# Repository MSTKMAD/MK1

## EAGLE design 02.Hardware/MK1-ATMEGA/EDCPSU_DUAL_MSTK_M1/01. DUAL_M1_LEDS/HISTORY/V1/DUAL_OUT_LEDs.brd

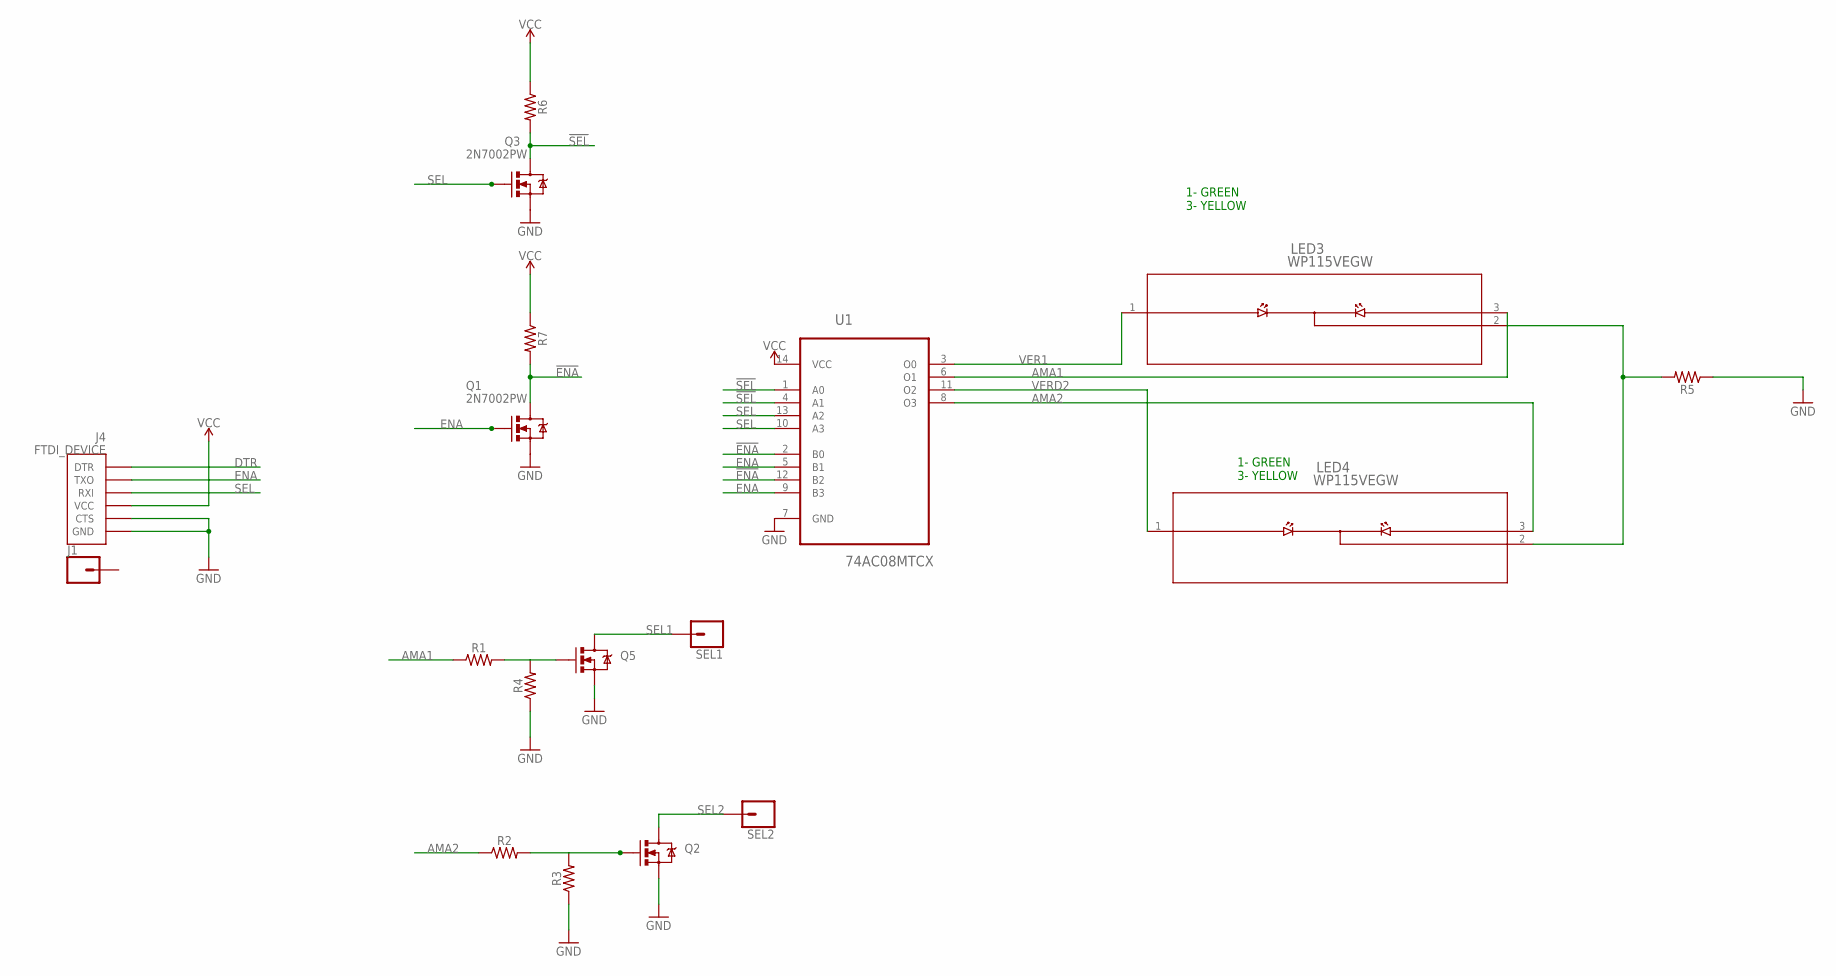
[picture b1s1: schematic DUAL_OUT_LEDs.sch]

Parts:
J1: CONN_01; 1X01
J4: FTDI_DEVICE; FTDI_DEVICE_SIDE
LED3, LED4: WP115VEGW; WP115VEGW_KNB
Q1, Q2, Q3, Q5: 2N7002PW; SOT323
R1, R2, R3, R4, R5, R6, R7: 0805
SEL1, SEL2: CONN_01; 1X01
U1: 74AC08MTCX; SOP65P640X120-14N

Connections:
!ENA!: Q1.3 (D), R7.2, U1.2 (B0), U1.12 (B2)
!SEL!: Q3.3 (D), R6.2, U1.1 (A0), U1.4 (A1)
AMA1: LED3.3, R1.1, U1.6 (O1)
AMA2: LED4.3, R2.1, U1.8 (O3)
DTR: J4.P$1 (DTR)
ENA: J4.P$2 (TXO), Q1.1 (G), U1.5 (B1), U1.9 (B3)
GND: J4.P$5 (CTS), J4.P$6 (GND), Q1.2 (S), Q2.2 (S), Q3.2 (S), Q5.2 (S), R3.1, R4.1, R5.1, U1.7 (GND)
unnamed: Q2.1 (G), R2.2, R3.2
unnamed: Q5.1 (G), R1.2, R4.2
unnamed: LED3.2, LED4.2, R5.2
SEL: J4.P$3 (RXI), Q3.1 (G), U1.10 (A3), U1.13 (A2)
SEL1: Q5.3 (D), SEL1.1
SEL2: Q2.3 (D), SEL2.1
VCC: J4.P$4 (VCC), R6.1, R7.1, U1.14 (VCC)
VER1: LED3.1, U1.3 (O0)
VERD2: LED4.1, U1.11 (O2)

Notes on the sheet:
1- GREEN 3- YELLOW

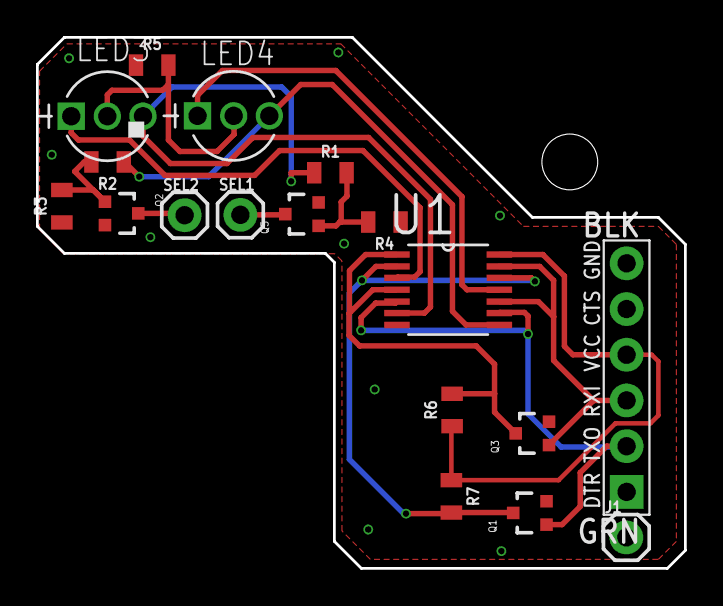
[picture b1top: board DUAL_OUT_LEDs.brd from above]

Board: 2 copper layers, 36.0 x 29.5 mm, 18 parts (0 on the bottom side), 15 nets.

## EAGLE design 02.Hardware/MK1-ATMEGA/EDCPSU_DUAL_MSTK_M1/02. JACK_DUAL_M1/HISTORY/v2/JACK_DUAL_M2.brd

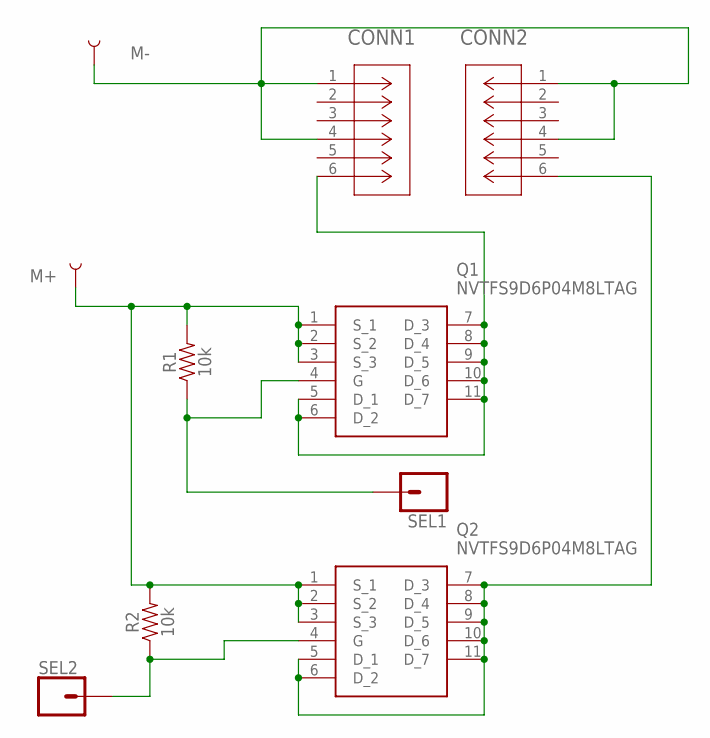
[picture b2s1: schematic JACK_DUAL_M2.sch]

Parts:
CONN1, CONN2: ACJS-MHDR; CONN_MHDR_AMP
M+: TEST-POINT3; PAD.03X.03
M-: TEST-POINT3; PAD.03X.03
Q1, Q2: NVTFS9D6P04M8LTAG; NVTFS5124PLTWG
R1, R2: 10k; 0805
SEL1, SEL2: CONN_01; 1X01

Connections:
GND: CONN1.1, CONN1.4, CONN2.1, CONN2.4, M-.P$1
M+: M+.P$1, Q1.1 (S_1), Q1.2 (S_2), Q1.3 (S_3), Q2.1 (S_1), Q2.2 (S_2), Q2.3 (S_3), R1.2, R2.2
M+2: CONN2.6, Q2.5 (D_1), Q2.6 (D_2), Q2.7 (D_3), Q2.8 (D_4), Q2.9 (D_5), Q2.10 (D_6), Q2.11 (D_7)
unnamed: CONN1.6, Q1.5 (D_1), Q1.6 (D_2), Q1.7 (D_3), Q1.8 (D_4), Q1.9 (D_5), Q1.10 (D_6), Q1.11 (D_7)
unnamed: Q1.4 (G), R1.1, SEL1.1
unnamed: Q2.4 (G), R2.1, SEL2.1

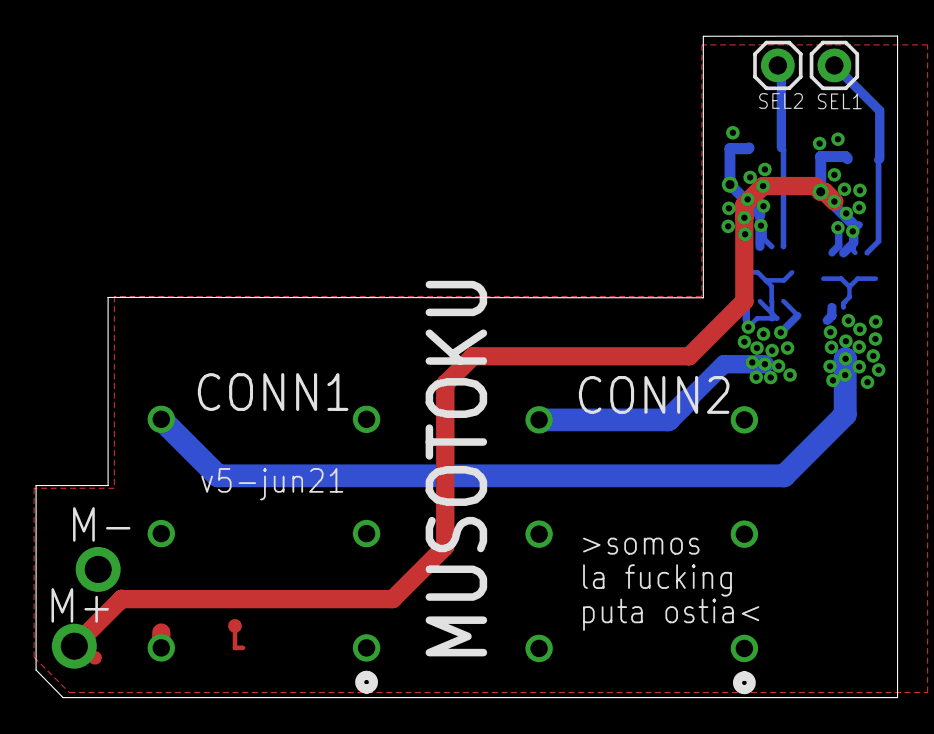
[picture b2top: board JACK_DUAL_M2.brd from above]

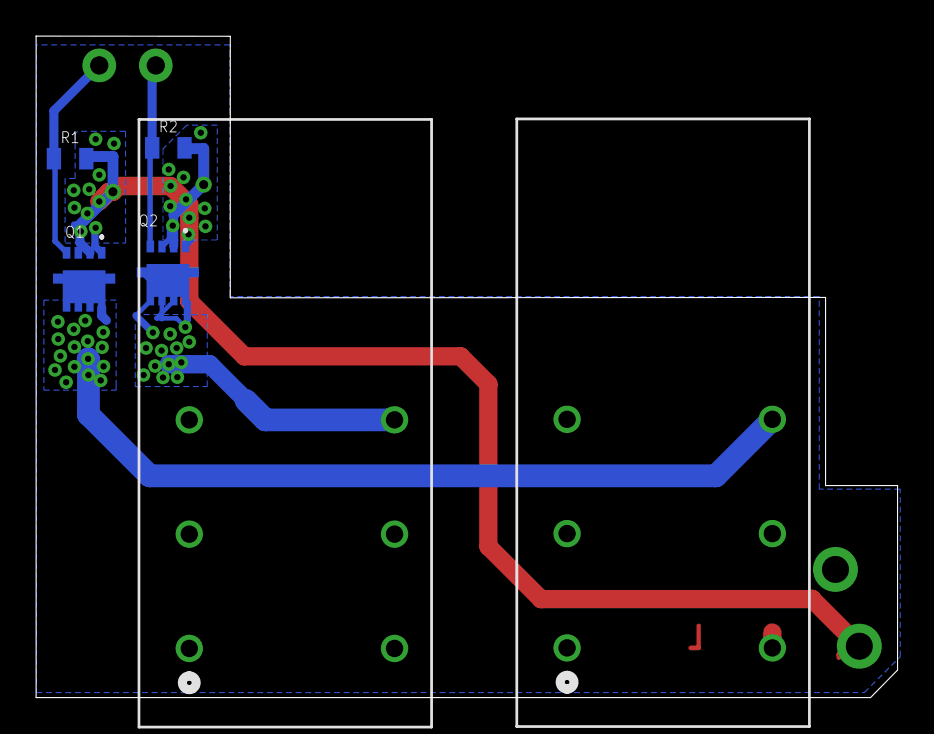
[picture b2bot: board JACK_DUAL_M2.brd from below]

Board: 2 copper layers, 47.9 x 36.8 mm, 10 parts (6 on the bottom side), 6 nets.

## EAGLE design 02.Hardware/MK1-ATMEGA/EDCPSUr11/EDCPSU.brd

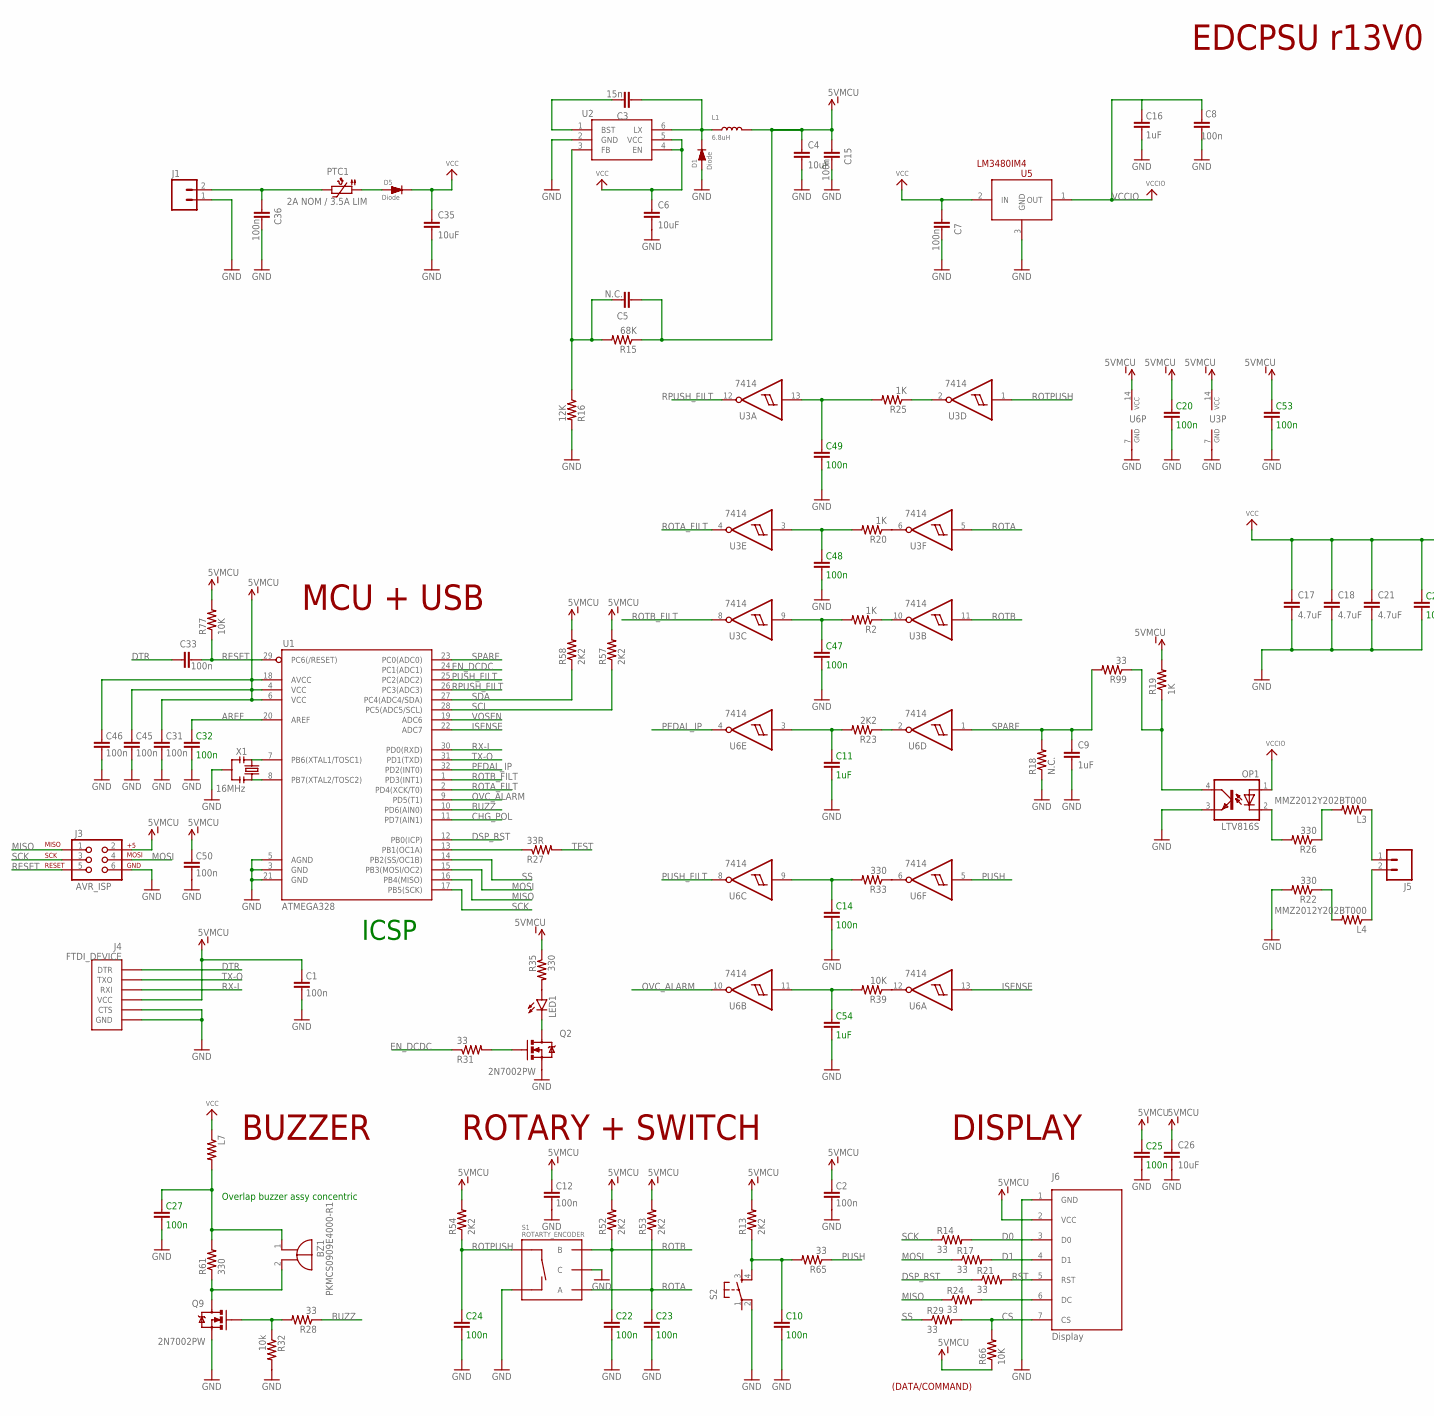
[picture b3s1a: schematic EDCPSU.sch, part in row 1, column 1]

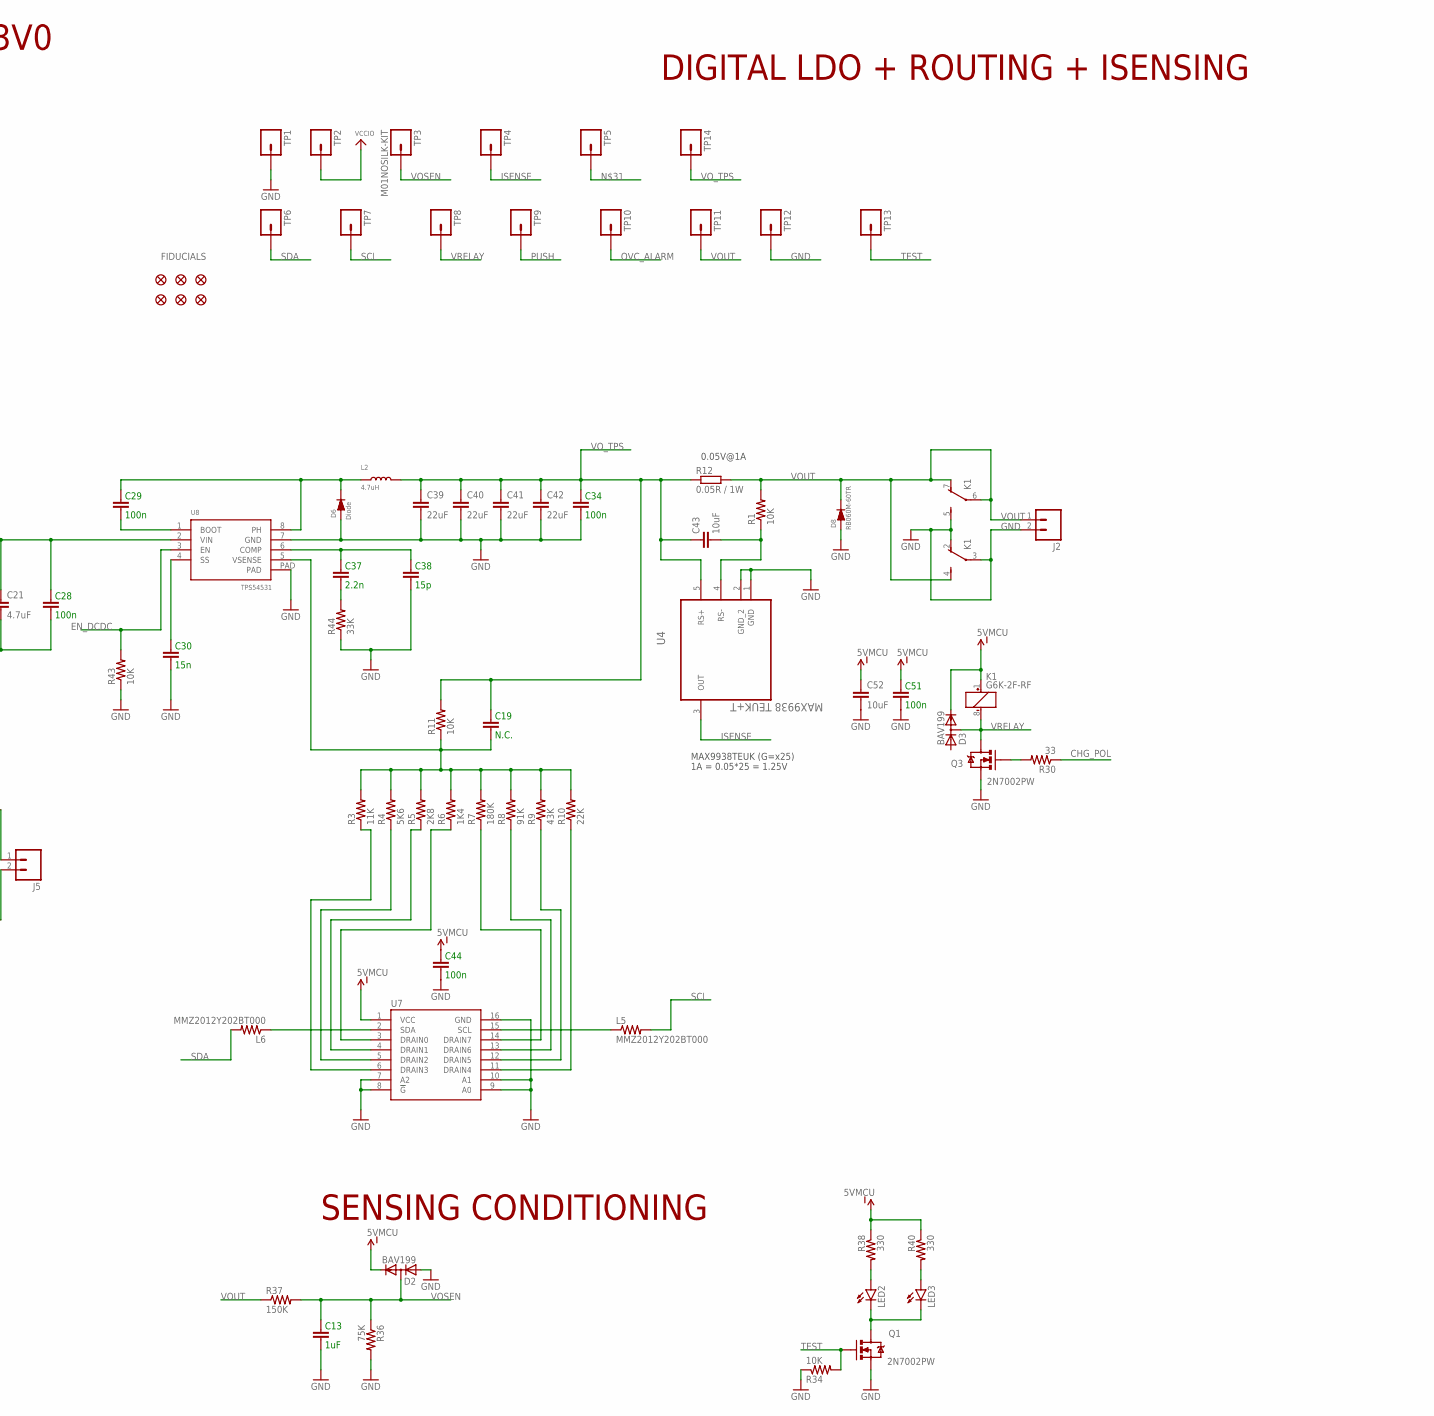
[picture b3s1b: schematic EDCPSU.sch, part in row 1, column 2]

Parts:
BZ1: PKMCS0909E4000-R1; PKMCS0909
C1, C2, C7, C8, C10, C12, C14, C15, C20, C22, C23, C24, C25, C27, C28, C29, C31, C32, C33, C34, C36, C44, C45, C46, C47, C48, C49, C50, C51, C53: 100n; 0805
C3, C30: 15n; 0805
C4, C6, C26, C35, C43, C52: 10uF; 1206
C5, C19: N.C.; 0805
C9: 1uF; 1206
C11, C13, C16, C54: 1uF; 0805
C17, C18, C21: 4.7uF; 1210
C37: 2.2n; 0805
C38: 15p; 0805
C39, C40, C41, C42: 22uF; 1210
D1: Diode; SOD123
D2, D3: BAV199; SOT23
D5, D6: Diode; DO-214AB
D8: RB060M-60TR; SMADIODE
FID1, FID2, FID3, FID4, FID5, FID6: FIDUCIAL1X2; FIDUCIAL-1X2
J1, J2, J5: M02LOCK_LONGPADS; 1X02_LOCK_LONGPADS
J3: AVR_ISP; 2X3
J4: FTDI_DEVICE; FTDI_DEVICE_SIDE
J6: Display; OLED_LCD
K1: G6K-2F-RF; G6K-RF
L1: 6.8uH; NR4018T100M
L2: 4.7uH; WE-LHMI
L3, L4, L5, L6, L7: MMZ2012Y202BT000; 0805
LED1: LED3MM
LED2, LED3: LED5MM
OP1: LTV816S; SMD4
PTC1: 2A NOM / 3.5A LIM; 1812L
Q1, Q2, Q3, Q9: 2N7002PW; SOT323
R1, R11, R34, R39, R43, R66, R77: 10K; 0805
R2, R19, R20, R25: 1K; 0805
R3: 11K; 0805
R4: 5K6; 0805
R5: 2K8; 0805
R6: 1K4; 0805
R7: 180K; 0805
R8: 91K; 0805
R9: 43K; 0805
R10: 22K; 0805
R12: 0.05R / 1W; R2512
R13, R23, R52, R53, R54, R57, R58: 2K2; 0805
R14, R17, R21, R24, R28, R29, R30, R31, R65, R99: 33; 0805
R15: 68K; 0805
R16: 12K; 0805
R18: N.C.; 0805
R22, R26: 330; 1206
R27: 33R; 0805
R32: 10k; 0805
R33, R35, R38, R40, R61: 330; 0805
R36: 75K; 0805
R37: 150K; 0805
R44: 33K; 0805
S1: ROTARTY_ENCODER; ROTARY_ENC_PLAIN
S2: TAC_SWITCH_KSC931G-SMD; TAC_SW_SMD_KSC931G
TP1, TP2, TP4, TP5, TP6, TP7, TP8, TP9, TP10, TP11, TP12, TP13, TP14: M01POGOPIN_HOLE_LARGE; 1X01_POGOPIN_HOLE_LARGE
TP3: M01NOSILK-KIT; 1X01NS-KIT
U1: ATMEGA328; TQFP32-08
U2: BD9G101G; SSOP6
U3, U6: 7414; TSSOP14
U4: MAX9938 TEUK+T; SOT95P280X145-5N
U5: LM3480IM4; SOT23-3
U7: TPIC2810D; SO16
U8: TPS54531; SOIC8
X1: 16MHz; RESONATOR-SMD

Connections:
AREF: C32.2, U1.20 (AREF)
BUZZ: R28.1, U1.10 (PD6(AIN0))
CHG_POL: R30.1, U1.11 (PD7(AIN1))
CS: J6.7 (CS), R29.2, R66.2
D0: J6.3 (D0), R14.2
D1: J6.4 (D1), R17.2
DSP_RST: R21.1, U1.12 (PB0(ICP))
DTR: C33.2, J4.P$1 (DTR)
EN_DCDC: R31.1, R43.2, U1.24 (PC1(ADC1)), U8.3 (EN)
GND: C1.1, C2.1, C4.2, C6.2, C7.1, C8.1, C9.2, C10.1, C11.1, C12.1, C13.1, C14.1, C15.1, C16.1, C17.2, C18.2, C20.1, C21.2, C22.1, C23.1, C24.1, C25.1, C26.2, C27.1, C28.1, C30.1, C31.1, C32.1, C34.1, C35.2, C36.1, C38.1, C39.2, C40.2, C41.2, C42.2, C44.1, C45.1, C46.1, C47.1, C48.1, C49.1, C50.1, C51.1, C52.2, C53.1, C54.1, D1.+ (A), D2.1 (A), D6.1 (A), D8.A, J1.1, J2.2, J3.6, J4.P$5 (CTS), J4.P$6 (GND), J6.1 (GND), K1.2 (O), K1.3, K1.5 (S), OP1.3 (EMIT), Q1.2 (S), Q2.2 (S), Q3.2 (S), Q9.2 (S), R16.2, R18.1, R22.2, R32.2, R34.1, R36.2, R43.1, R44.1, S1.C, S1.SW-, S2.2, TP1.1, TP12.1, U1.3 (GND), U1.5 (AGND), U1.21 (GND), U2.2 (GND), U3.7 (GND), U4.1 (GND), U4.2 (GND_2), U5.3 (GND), U6.7 (GND), U7.7 (A2), U7.8 (!G), U7.9 (A0), U7.10 (A1), U7.16 (GND), U8.7 (GND), U8.PAD, X1.2
ISENSE: TP4.1, U1.22 (ADC7), U4.3 (OUT), U6.13 (I)
MISO: J3.1, R24.1, U1.16 (PB4(MISO))
MOSI: J3.4, R17.1, U1.15 (PB3(MOSI/OC2))
unnamed: R3.1, U7.6 (DRAIN3)
unnamed: R4.1, U7.5 (DRAIN2)
unnamed: R5.1, U7.4 (DRAIN1)
unnamed: R6.1, U7.3 (DRAIN0)
unnamed: R7.1, U7.14 (DRAIN7)
unnamed: J6.6 (DC), R24.2
unnamed: R8.1, U7.13 (DRAIN6)
unnamed: R9.1, U7.12 (DRAIN5)
unnamed: R10.1, U7.11 (DRAIN4)
unnamed: C43.2, R1.1, U4.4 (RS-)
unnamed: LED1.A, R35.2
unnamed: LED1.K (C), Q2.3 (D)
unnamed: R33.1, U6.6 (O)
unnamed: D5.1 (A), PTC1.1
unnamed: R39.1, U6.12 (O)
unnamed: C3.1, U2.1 (BST)
unnamed: C10.2, R13.1, R65.2, S2.4
unnamed: C47.2, R2.2, U3.9 (I)
unnamed: C3.2, D1.- (K), L1.1, U2.6 (LX)
unnamed: Q9.1 (G), R28.2, R32.1
unnamed: Q2.1 (G), R31.2
unnamed: R2.1, U3.10 (O)
unnamed: R20.1, U3.6 (O)
unnamed: U1.8 (PB7(XTAL2/TOSC2)), X1.1
unnamed: R25.1, U3.2 (O)
unnamed: C49.2, R25.2, U3.13 (I)
unnamed: C5.1, R15.2, R16.1, U2.3 (FB)
unnamed: C48.2, R20.2, U3.3 (I)
unnamed: C11.2, R23.2, U6.3 (I)
unnamed: R27.1, U1.13 (PB1(OC1A))
unnamed: OP1.4 (COL), R19.1, R99.1, TP5.1
unnamed: BZ1.1 (+), C27.2, L7.2, R61.2
unnamed: C36.2, J1.2, PTC1.2
unnamed: R23.1, U6.2 (O)
unnamed: U1.7 (PB6(XTAL1/TOSC1)), X1.3
unnamed: C14.2, R33.2, U6.9 (I)
unnamed: LED2.A, R38.2
unnamed: C54.2, R39.2, U6.11 (I)
unnamed: L6.1, U7.2 (SDA)
unnamed: OP1.2 (C), R26.2
unnamed: Q3.1 (G), R30.2
unnamed: L3.2, R26.1
unnamed: C30.2, U8.4 (SS)
unnamed: L4.2, R22.1
unnamed: C29.1, U8.1 (BOOT)
unnamed: C19.1, R3.2, R4.2, R5.2, R6.2, R7.2, R8.2, R9.2, R10.2, R11.1, U8.5 (VSENSE)
unnamed: LED3.A, R40.2
unnamed: C29.2, D6.2 (K), L2.1, U8.8 (PH)
unnamed: C37.2, C38.2, U8.6 (COMP)
unnamed: C37.1, R44.2
unnamed: L5.1, U7.15 (SCL)
unnamed: J5.1, L3.1
unnamed: J5.2, L4.1
unnamed: LED2.K (C), LED3.K (C), Q1.3 (D)
unnamed: BZ1.2 (-), Q9.3 (D), R61.1
OVC_ALARM: TP10.1, U1.9 (PD5(T1)), U6.10 (O)
PEDAL_IP: U1.32 (PD2(INT0)), U6.4 (O)
PUSH: R65.1, TP9.1, U6.5 (I)
PUSH_FILT: U1.25 (PC2(ADC2)), U6.8 (O)
RESET: C33.1, J3.5, R77.1, U1.29 (PC6(/RESET))
ROTA: C23.2, R53.1, S1.A, U3.5 (I)
ROTA_FILT: U1.2 (PD4(XCK/T0)), U3.4 (O)
ROTB: C22.2, R52.1, S1.B, U3.11 (I)
ROTB_FILT: U1.1 (PD3(INT1)), U3.8 (O)
ROTPUSH: C24.2, R54.1, S1.SW+, U3.1 (I)
RPUSH_FILT: U1.26 (PC3(ADC3)), U3.12 (O)
RST: J6.5 (RST), R21.2
RX-I: J4.P$3 (RXI), U1.30 (PD0(RXD))
SCK: J3.3, R14.1, U1.17 (PB5(SCK))
SCL: L5.2, R57.1, TP7.1, U1.28 (PC5(ADC5/SCL))
SDA: L6.2, R58.1, TP6.1, U1.27 (PC4(ADC4/SDA))
SPARE: C9.1, R18.2, R99.2, U1.23 (PC0(ADC0)), U6.1 (I)
SS: R29.1, U1.14 (PB2(SS/OC1B))
TEST: Q1.1 (G), R27.2, R34.2, TP13.1
TX-O: J4.P$2 (TXO), U1.31 (PD1(TXD))
VCC: C6.1, C7.2, C17.1, C18.1, C21.1, C28.2, C35.1, D5.2 (K), L7.1, U2.4 (EN), U2.5 (VCC), U5.2 (IN), U8.2 (VIN)
VCC-ISO: C1.2, C2.2, C4.1, C5.2, C12.2, C15.2, C20.2, C25.2, C26.1, C31.2, C44.2, C45.2, C46.2, C50.2, C51.2, C52.1, C53.2, D2.2 (C), D3.2 (C), J3.2, J4.P$4 (VCC), J6.2 (VCC), K1.1 (+), L1.2, R13.2, R15.1, R19.2, R35.1, R38.1, R40.1, R52.2, R53.2, R54.2, R57.2, R58.2, R66.1, R77.2, U1.4 (VCC), U1.6 (VCC), U1.18 (AVCC), U3.14 (VCC), U6.14 (VCC), U7.1 (VCC)
VCCIO: C8.2, C16.2, OP1.1 (A), TP2.1, U5.1 (OUT)
VOSEN: C13.2, D2.3 (AC), R36.1, R37.2, TP3.1, U1.19 (ADC6)
VOUT: D8.C (K), J2.1, K1.4 (S), K1.6, K1.7 (O), R1.2, R12.2, R37.1, TP11.1
VO_TPS: C19.2, C34.2, C39.1, C40.1, C41.1, C42.1, C43.1, L2.2, R11.2, R12.1, TP14.1, U4.5 (RS+)
VRELAY: D3.3 (AC), K1.8 (-), Q3.3 (D), TP8.1

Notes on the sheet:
0.05V@1A
SENSING CONDITIONING
DIGITAL LDO + ROUTING + ISENSING
MCU + USB
EDCPSU r13V0
(DATA/COMMAND)
Overlap buzzer assy concentric
ICSP
BUZZER
ROTARY + SWITCH
DISPLAY
FIDUCIALS
MAX9938TEUK (G=x25)
1A = 0.05*25 = 1.25V

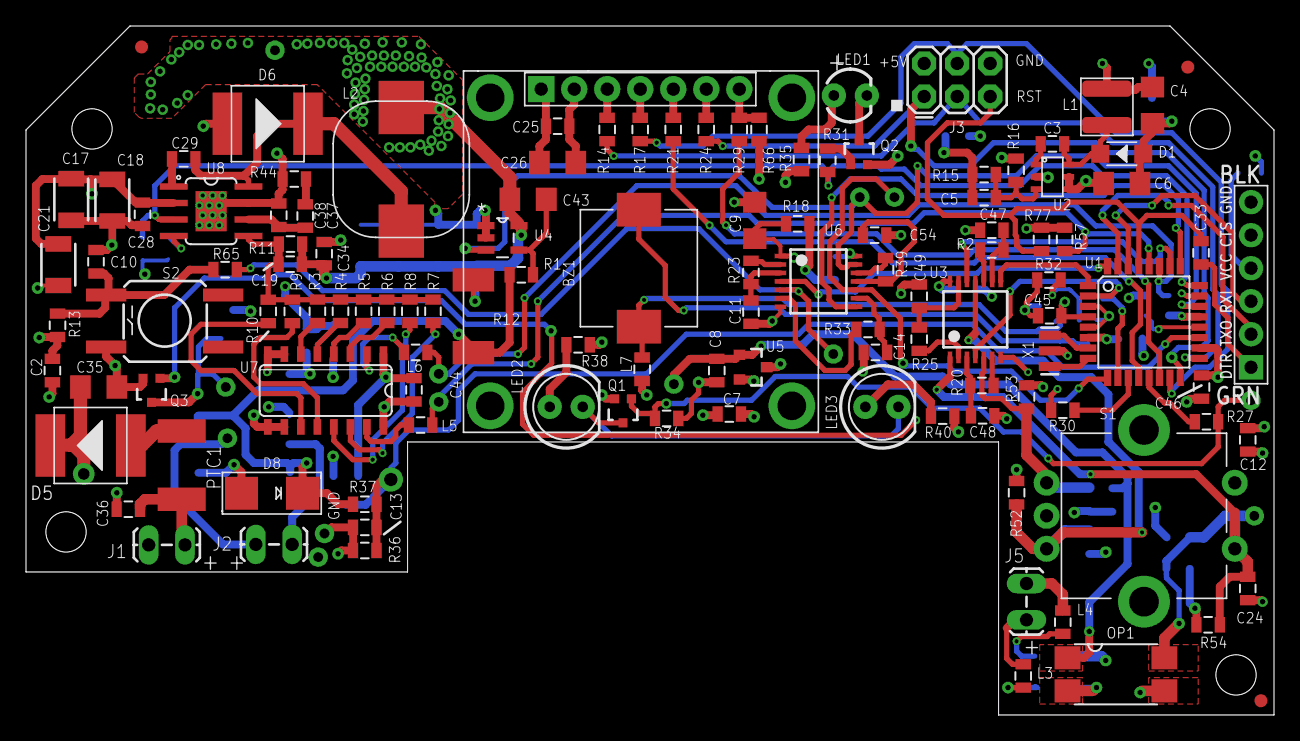
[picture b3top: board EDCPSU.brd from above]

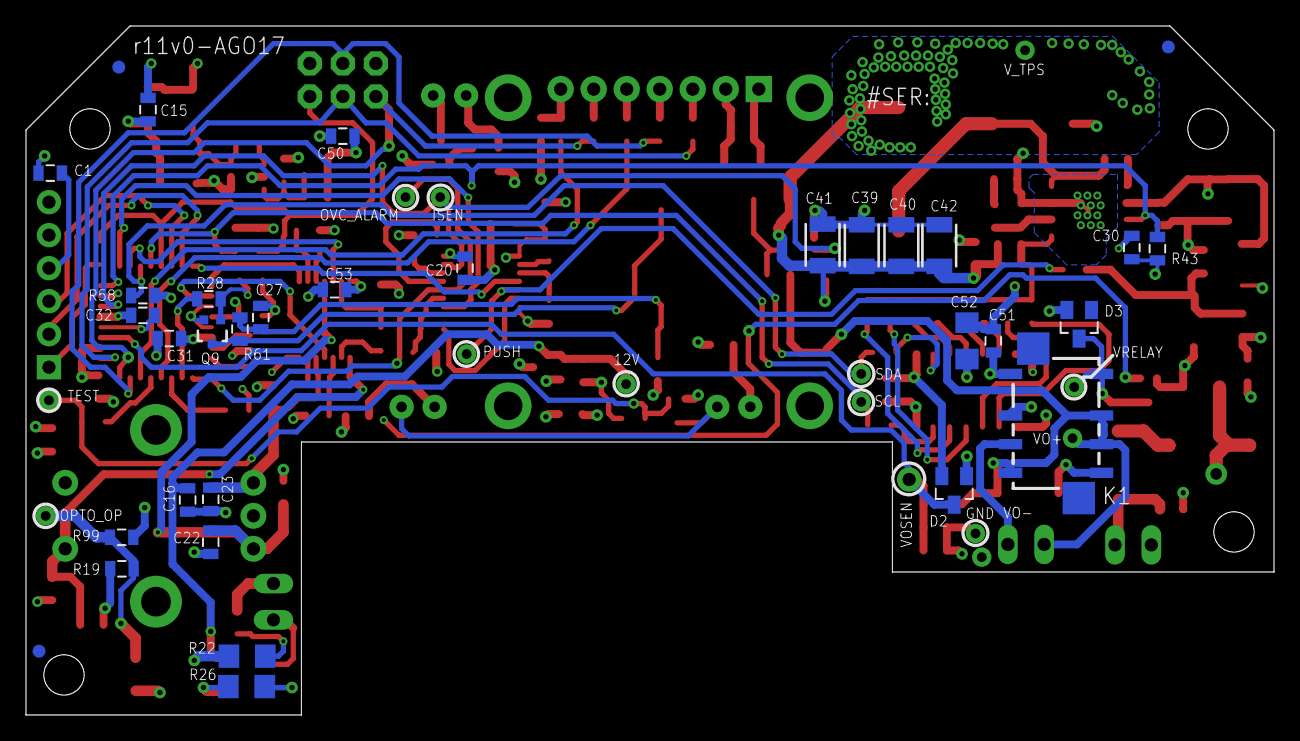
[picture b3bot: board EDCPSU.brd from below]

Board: 4 copper layers, 96.0 x 53.0 mm, 167 parts (33 on the bottom side), 95 nets.

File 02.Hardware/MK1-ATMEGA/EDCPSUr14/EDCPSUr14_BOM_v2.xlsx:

|  |  |  |  |  | BOM VERSION v2
 |  |  |  |  |  | 44080
 |  |  |  |  |  | EDCPSU_r14v0
Assembly? | Pos | Qty | Parts | Value | Device | Package | Description | Details | DIGIKEY | COST (25pcs) | COST (100pcs) | COST per Board (25pcs)
P | 1 | 1 | R12 | 0.05R / 1W | Resistor | 2512 | Current sense resistor | 1W, 1%, 75ppm | 985-1555-1-ND | 0.27 | 0.18 | 0.27
P | 2 | 6 | R1, R32, R39, R42, R66, R77 | 10K | Resistor | 805 | Resistor | 0.05 |  |  |  | 0
P | 3 | 1 | R11 | 15K | Resistor | 805 | Resistor | 0.05
P | 4 | 1 | R3 | 11K | Resistor | 805 | Resistor | 0.05 |  |  |  | 0
P | 5 | 1 | R7 | 180K | Resistor | 805 | Resistor | 0.05 |  |  |  | 0
P | 6 | 4 | R2, R19, R20, R25 | 1K | Resistor | 805 | Resistor | 0.05 |  |  |  | 0
P | 7 | 1 | R6 | 1K4 | Resistor | 805 | Resistor | 0.05 |  |  |  | 0
P | 8 | 1 | R16 | 12K | Resistor | 805 | Resistor | 0.05 |  |  |  | 0
P | 9 | 1 | R37 | 220K | Resistor | 805 | Resistor | 0.05 |  |  |  | 0
P | 10 | 1 | R10 | 22K | Resistor | 805 | Resistor | 0.05 |  |  |  | 0
P | 11 | 7 | R13, R23, R52, R53, R54, R57, R58 | 2K2 | Resistor | 805 | Resistor | 0.05 |  |  |  | 0
P | 12 | 1 | R5 | 2K8 | Resistor | 805 | Resistor | 0.05 |  |  |  | 0
P | 13 | 11 | R14, R17, R21, R24, R28, R29, R30, R31, R65, R99, R45 | 33 | Resistor | 805 | Resistor | 0.05 |  |  |  | 0
P | 14 | 6 | R27, R33, R35, R61 | 330 | Resistor | 805 | Resistor | 0.05 |  |  |  | 0
P | 15 | 2 | R22, R26 | 330 | Resistor | 1206 | Resistor | 0.05 |  |  |  | 0
P | 16 | 1 | R44 | 33K | Resistor | 805 | Resistor | 0.05 |  |  |  | 0
P | 17 | 1 | R9 | 43K | Resistor | 805 | Resistor | 0.05 |  |  |  | 0
P | 18 | 1 | R4 | 5K6 | Resistor | 805 | Resistor | 0.05 |  |  |  | 0
P | 19 | 1 | R15 | 68K | Resistor | 805 | Resistor | 0.05 |  |  |  | 0
P | 20 | 1 | R36 | 75K | Resistor | 805 | Resistor | 0.05 |  |  |  | 0
P | 21 | 1 | R8 | 91K | Resistor | 805 | Resistor | 0.05 |  |  |  | 0
P | 22 | 30 | C1, C2, C7, C8, C10, C12, C14, C15, C20, C22, C23, C24, C25, C27, C28, C29, C31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 | 100n | Capacitor | 805 | Capacitor | 25V-50V, X7R or XR5 |  |  |  | 0
P | 23 | 6 | C4, C6, C26, C35, C43, C52 | 10uF | Capacitor | 1206 | Capacitor | 25V-50V, X7R or XR5 |  |  |  | 0
P | 24 | 2 | C3, C30 | 15n | Capacitor | 805 | Capacitor | 25V-50V, X7R or XR5 |  |  |  | 0
P | 25 | 1 | C38 | 15p | Capacitor | 805 | Capacitor | 25V-50V, X7R or XR5 |  |  |  | 0
P | 26 | 4 | C11, C13, C16, C54 | 1uF | Capacitor | 805 | Capacitor | 25V-50V, X7R or XR5 |  |  |  | 0
P | 27 | 1 | C9 | 1uF | Capacitor | 1206 | Capacitor | 25V-50V, X7R or XR5 |  |  |  | 0
P | 28 | 1 | C37 | 2.2n | Capacitor | 805 | Capacitor | 25V-50V, X7R or XR5 |  |  |  | 0
P | 29 | 4 | C39, C40, C41, C42 | 22uF | Capacitor | 1210 | Capacitor | 25V, X5R | 490-6540-1-ND | 0.31 |  | 1.24
P | 30 | 3 | C17, C18, C21 | 4.7uF | Capacitor | 1206 | Capacitor | 50V, 10% X7R | 1276-2789-1-ND | 0.18 | 0.14000000000000001 | 0.54
P | 31 | 1 | L2 | 4.7uH | inductor | WE-LHMI |  | 4.7uH, 7A 0.0155 OHM | 732-3389-1-ND | 2.96 | 2.5 | 2.96
P | 32 | 1 | L1 | 6.8uH | Inductor | NR4018T100M | Inductor | 6.8uH, 1A, 0.132R | 587-2657-1-ND | 0.25 | 0.2 | 0.25
P | 33 | 5 | L3, L4, L5, L6, L7 | MMZ2012Y202BT000 | Inductor | 805 | Inductor | FERRITE CHIP 2000 OHM 400MA | 445-1561-1-ND | 0.08 | 4.4999999999999998E-2 | 0.4
P | 34 | 2 | U3, U6 | SN74AC14DBR | integrated Circuit | SSOP14 | Hex schmitt trigger INVERTER |  | 296-4299-1-ND | 0.38 | 0.28000000000000003 | 0.76
P | 35 | 1 | U1 | ATMEGA328P-AU | integrated Circuit | 32-TQFP | MCU 8BIT 32KB FLASH 32TQFP |  | ATMEGA328P-AU-ND | 2.8 | 2.56 | 2.8
P | 36 | 1 | U5 | LM3480IM3X-12 | integrated Circuit | SOT23-3 | Small package linear regulator |  | LM3480IM3X-12/NOPBCT-ND | 0.76 | 0.66 | 0.76
P | 37 | 1 | U4 | MAX9938TEUK+TCT-ND | integrated Circuit | SOT23-5 | Current sense amplifier | X25 GAIN | MAX9938TEUK+TCT-ND | 1 | 0.93 | 1
P | 38 | 1 | U2 | BD9G101G | integrated Circuit | SSOP6 | BD9G101G - Simple Step-down |  | BD9G101G-CT-ND | 1.26 | 1.1100000000000001 | 1.26
P | 39 | 1 | U7 | TPIC2810D | integrated Circuit | SO16 | I2C Led driver |  | 296-21426-5-ND | 1.4 | 1.1299999999999999 | 1.4
P | 40 | 1 | U8 | TPS54531DDAR | Integrated Circuit | SOIC8 | BUCK converter |  | 296-40801-1-ND | 2.2000000000000002 | 1.45 | 2.2000000000000002
P | 41 | 1 | X1 | 16MHz | RESONATORSMD | 3-SMD, Non-Standard | CER RESONATOR 16.00MHZ SMD | 16MHz | 490-1198-1-ND | 0.39 | 0.31 | 0.39
P | 42 | 1 | S2 | TAC_SWITCH_KSC931G-SMD | pushbutton | TAC_SW_SMD_KSC931G | Momentary Switch |  | CKN10432CT-ND | 0.73 | 0.61 | 0.73
P | 43 | 1 | PTC1 | 1,5A HOLD / 3A LIM | PTC | 1812 | PTC RESTTBLE 1.50A 24V CHIP 1812 | 1,5A | 507-1505-1-ND | 0.24 | 0.22 | 0.24
P | 44 | 4 | Q2, Q3, Q4, Q9 | 2N7002PW | transistor | SOT323 | MOSFET N-CH 60V 0.31A, 1.6 Ohm. 2.4 VGS |  | 568-5987-1-ND | 0.24 | 0.18 | 0.96
P | 45 | 2 | D2, D3 | BAV199 | diode | SOT23 | DIODE |  | BAV199INCT-ND | 0.18 | 0.08 | 0.36
P | 46 | 2 | D5, D6 | Diode | diode | DO-214AB | SCHOTTKY 40V 5A DO214AB |  | SK54L-TPMSCT-ND | 0.35 | 0.3 | 0.7
P | 47 | 1 | D1 | RB060M-60TR | diode | PMDU | DIODE SCHOTTKY 60V 2A PMDU |  | RB060M-60CT-ND | 0.3 | 0.19 | 0.3
P | 48 | 1 | D8 | B220A-13-F | diode | DO-214AC | DIODE SCHOTTKY 20V 2A SMA |  | B220A-FDICT-ND | 0.31 | 0.19 | 0.31
P | 49 | 1 | OP1 | LTV816S | Integrated Circuit | SMD4 Gullwing | OPTO COUPLER | CTRmin=50% @ 5mA, 5KViso | 160-1361-5-ND | 0.28000000000000003 | 0.18 | 0.28000000000000003
P | 50 | 1 | BZ1 | PKMCS0909E4000-R1 | speaker | SMD | Buzzer 12V |  | 490-9647-1-ND | 1.08 | 0.96799999999999997 | 1.08
 | 51
NO | 52 | 1 | S1 | ROTARTY_ENCODER | ROTARTY_ENCODER | ROTARY_ENC_PLAIN | Simple no LED rotary encoder
NO | 53 | 1 | LED1 | LED thru hole | LED3MM | LED3MM | LED Yellow
NO | 54 | 13 | TP1, TP2, TP4, TP5, TP6, TP7, TP8, TP9, TP10, TP11, TP12, TP13, TP14 | Test point
NO | 55 | 1 | DC1 | 12V to 5V | NME | NME | DC-DC CONVERTER
NO | 56 | 2 | C5, C19 | N.C. | CAP0805 | 805 | Capacitor
NO | 57 | 1 | R18 | N.C. | RESISTOR0805-RES | 805 | Resistor
NO | 58 | 1 | BZ2 | MCKPT-1340 | BUZZER_MCKPT-1340 | MCKPT-1340 | Buzzer 12V
NO | 59 | 1 | J4 | Connector | Connnector |  | Connector which mates to FTDI basic or FTDI cable.
NO | 60 | 1 | K1 | G6K-2F-RF | RELAY | G6K-RF | OMRON High Frequency Relay G6K-RF
NO | 61 | 1 | LK1 | ISO_12V | LINK | PAD-JUMPER-2-NO_YES_SILK
NO | 62 | 1 | J6 | Display | OLED_LCD | OLED_LCD
NO | 63 | 1 | J3 | Connector | CONNECTOR | 2X3_LOCK | AVR ISP 6 Pin
NO | 64 | 1 | LED2 | LED thru hole | LED 5MM | LED 5MM
NO | 65 |  | LED3
 | 66 | 1 | R41 | 330k | RESISTOR0805-RES | SMD0805 | Resistor | 0.05
 | 67 | 1 | R43 | 27k | RESISTOR0805-RES | SMD0805 | Resistor | 0.05
 | 68 | 1 | D4 | BZT52-B5V6J | DIODE | SOD-123 | Zener diode 5V6 590mW 2% 40ohm | 0.02 | Mouser |  | 5.3999999999999999E-2
NO | 69 | 0 | R46 | N.C. | RESISTOR0805-RES | SMD0805 | Resistor | 0.05

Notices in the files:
parts and their libraries:
SparkFun-Connectors: Licensing: Creative Commons ShareAlike 4.0 International - https://creativecommons.org/licenses/by-sa/4.0
COPYRIGHT: Copyright (C) 2018 Accelerated Designs. All rights reserved
